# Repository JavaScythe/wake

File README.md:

The best alarm clock you'll ever meet.

An alexa without a microphone.

- 35 neopixels
- ESP32 with wifi
- Speaker
- Buzzer
- Projector

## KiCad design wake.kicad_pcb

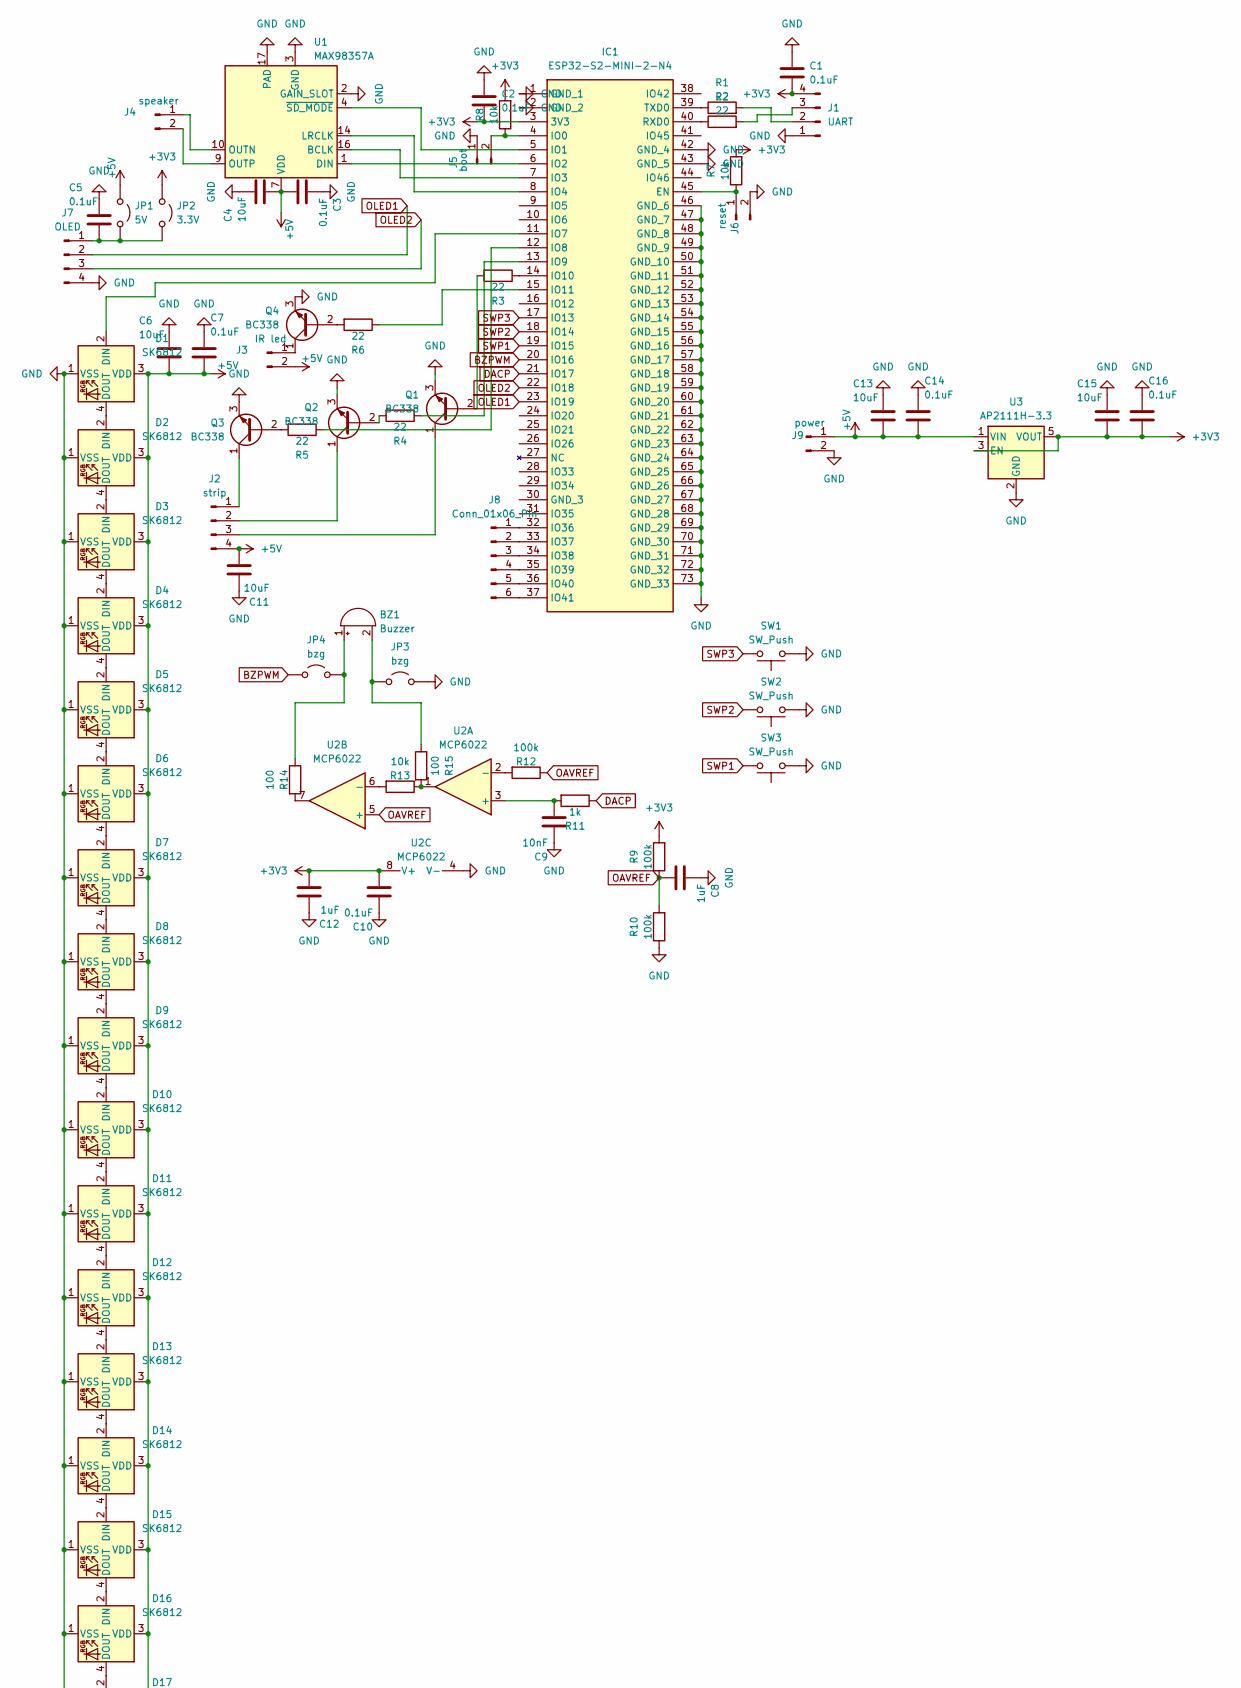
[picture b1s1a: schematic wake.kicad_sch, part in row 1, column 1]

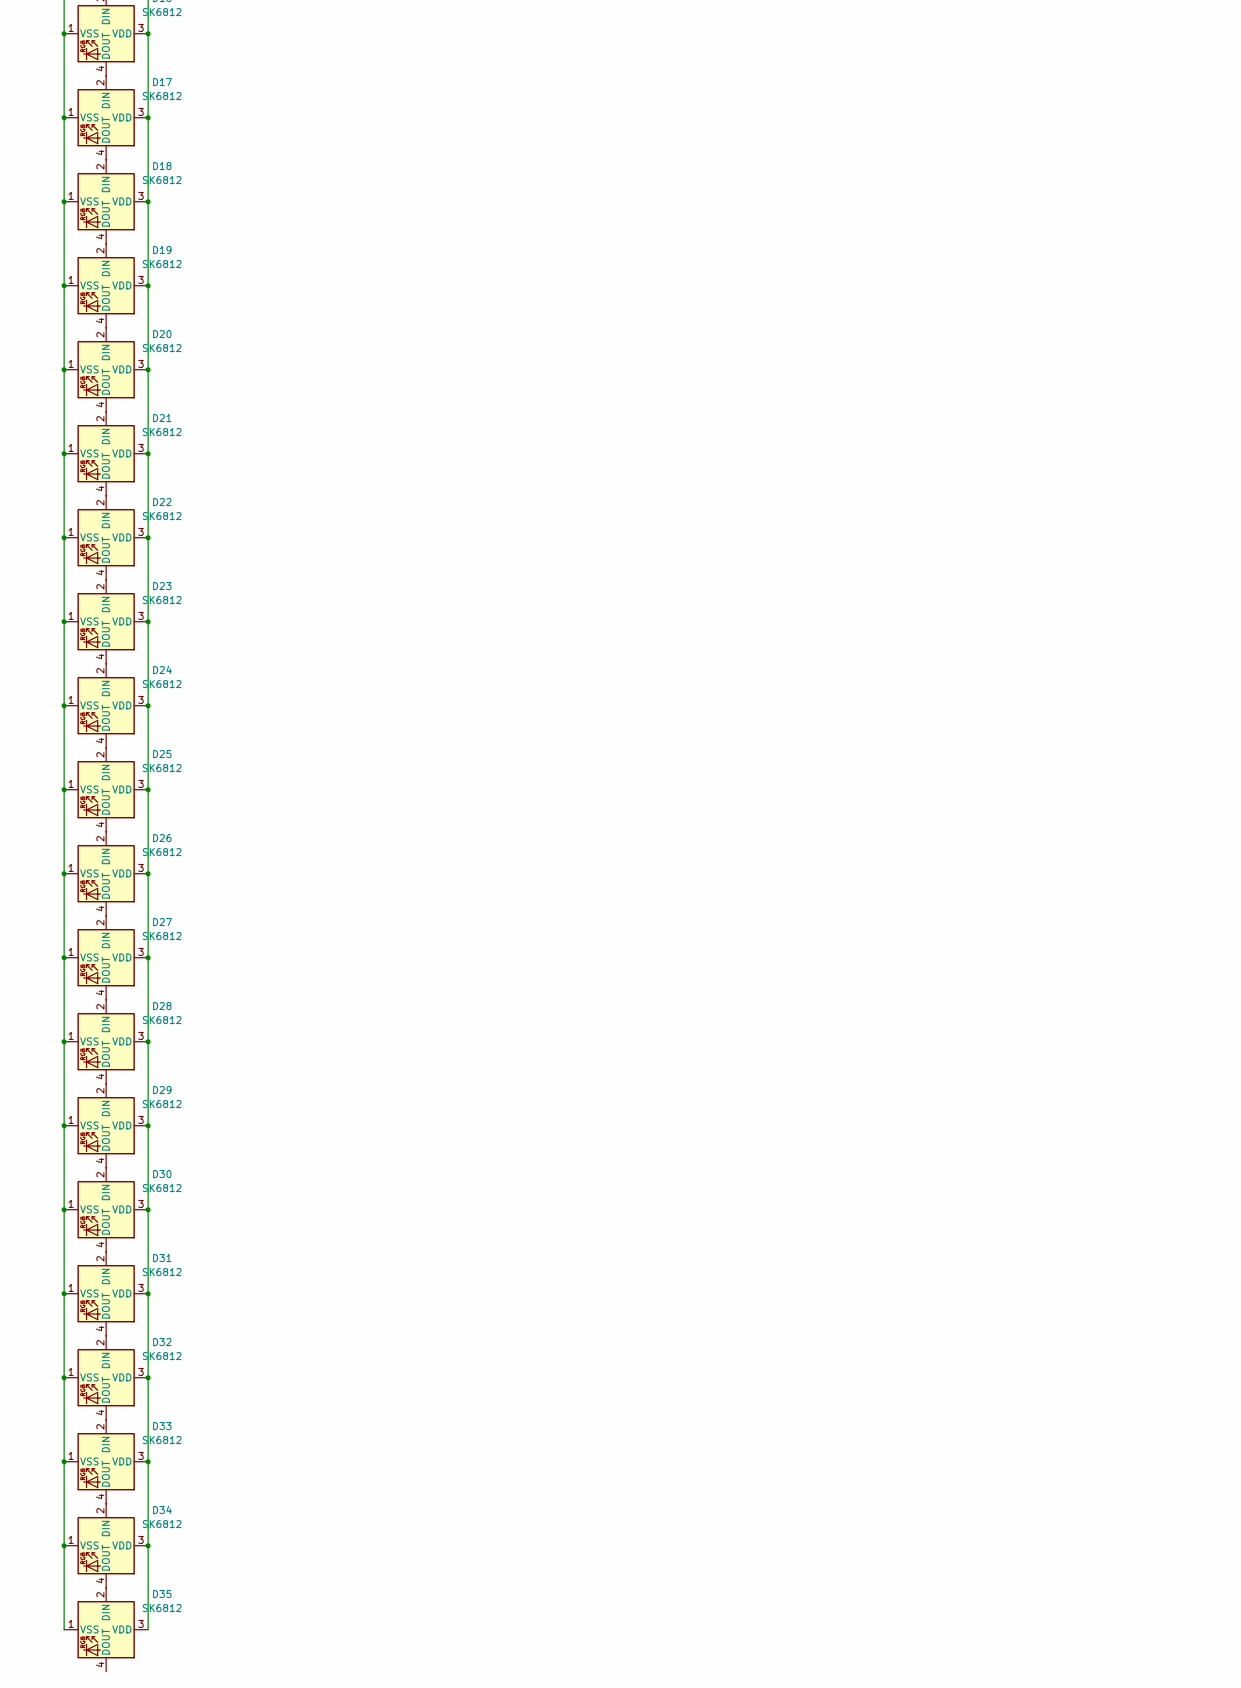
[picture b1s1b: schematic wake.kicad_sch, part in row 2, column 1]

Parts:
BZ1: Buzzer; Buzzer_12x9.5RM7.6
C1, C2, C3, C5, C7, C10, C14, C16: 0.1uF; C_0402_1005Metric
C4, C6, C11, C13, C15: 10uF; C_0402_1005Metric
C8, C12: 1uF; C_0402_1005Metric
C9: 10nF; C_0402_1005Metric
D1, D2, D3, D4, D5, D6, D7, D8, D9, D10, D11, D12, D13, D14, D15, D16, D17, D18, D19, D20, D21, D22, D23, D24, D25, D26, D27, D28, D29, D30, D31, D32, D33, D34, D35: SK6812; LED_SK6812_PLCC4_5.0x5.0mm_P3.2mm
IC1: ESP32-S2-MINI-2-N4; ESP32S2MINI2N4; Mouser Part Number 356-ESP32MINI-2-N4
J1: UART; PinHeader_1x04_P2.54mm_Vertical
J2: strip; PinHeader_1x04_P2.54mm_Vertical
J3: IR led; PinHeader_1x02_P2.54mm_Vertical
J4: speaker; PinHeader_1x02_P2.54mm_Vertical
J5: boot; PinHeader_1x02_P2.54mm_Vertical
J6: reset; PinHeader_1x02_P2.54mm_Vertical
J7: OLED; PinHeader_1x04_P2.54mm_Vertical
J8: Conn_01x06_Pin; PinHeader_1x06_P2.54mm_Vertical
J9: power; PinHeader_1x02_P2.54mm_Vertical
JP1: 5V; SolderJumper-2_P1.3mm_Open_TrianglePad1.0x1.5mm
JP2: 3.3V; SolderJumper-2_P1.3mm_Open_TrianglePad1.0x1.5mm
JP3, JP4: bzg; SolderJumper-2_P1.3mm_Open_TrianglePad1.0x1.5mm
Q1, Q2, Q3, Q4: BC338; TO-92_Inline
R1, R2, R3, R4, R5, R6: 22; R_0402_1005Metric
R7, R8, R13: 10k; R_0402_1005Metric
R9, R10, R12: 100k; R_0402_1005Metric
R11: 1k; R_0402_1005Metric
R14, R15: 100; R_0402_1005Metric
SW1, SW2, SW3: SW_Push; SW-SMD_4P-L12.0-W12.0-P5.00-LS15.5
U1: MAX98357A; TQFN-16-1EP_3x3mm_P0.5mm_EP1.23x1.23mm
U2: MCP6022; SOP-8_3.9x4.9mm_P1.27mm
U3: AP2111H-3.3; SOT-223

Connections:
+3V3: C1.2, C2.2, C10.2, C12.2, C15.2, C16.2, IC1.3 (3V3), J1.4, JP2.1 (A), R7.2, R8.2, R9.2, U2.8 (V+), U3.3 (EN), U3.5 (VOUT)
+5V: C3.2, C4.2, C6.2, C7.2, C11.2, C13.2, C14.2, D1.3 (VDD), D2.3 (VDD), D3.3 (VDD), D4.3 (VDD), D5.3 (VDD), D6.3 (VDD), D7.3 (VDD), D8.3 (VDD), D9.3 (VDD), D10.3 (VDD), D11.3 (VDD), D12.3 (VDD), D13.3 (VDD), D14.3 (VDD), D15.3 (VDD), D16.3 (VDD), D17.3 (VDD), D18.3 (VDD), D19.3 (VDD), D20.3 (VDD), D21.3 (VDD), D22.3 (VDD), D23.3 (VDD), D24.3 (VDD), D25.3 (VDD), D26.3 (VDD), D27.3 (VDD), D28.3 (VDD), D29.3 (VDD), D30.3 (VDD), D31.3 (VDD), D32.3 (VDD), D33.3 (VDD), D34.3 (VDD), D35.3 (VDD), J2.4, J3.2, J9.1, JP1.1 (A), U1.7 (VDD), U1.8 (VDD), U3.1 (VIN)
BZPWM: IC1.20 (IO16), JP4.1 (A)
DACP: IC1.21 (IO17), R11.1
GND: C1.1, C2.1, C3.1, C4.1, C5.1, C6.1, C7.1, C8.1, C9.1, C10.1, C11.1, C12.1, C13.1, C14.1, C15.1, C16.1, D1.1 (VSS), D2.1 (VSS), D3.1 (VSS), D4.1 (VSS), D5.1 (VSS), D6.1 (VSS), D7.1 (VSS), D8.1 (VSS), D9.1 (VSS), D10.1 (VSS), D11.1 (VSS), D12.1 (VSS), D13.1 (VSS), D14.1 (VSS), D15.1 (VSS), D16.1 (VSS), D17.1 (VSS), D18.1 (VSS), D19.1 (VSS), D20.1 (VSS), D21.1 (VSS), D22.1 (VSS), D23.1 (VSS), D24.1 (VSS), D25.1 (VSS), D26.1 (VSS), D27.1 (VSS), D28.1 (VSS), D29.1 (VSS), D30.1 (VSS), D31.1 (VSS), D32.1 (VSS), D33.1 (VSS), D34.1 (VSS), D35.1 (VSS), IC1.1 (GND_1), IC1.2 (GND_2), IC1.42 (GND_4), IC1.43 (GND_5), IC1.46 (GND_6), IC1.47 (GND_7), IC1.48 (GND_8), IC1.49 (GND_9), IC1.50 (GND_10), IC1.51 (GND_11), IC1.52 (GND_12), IC1.53 (GND_13), IC1.54 (GND_14), IC1.55 (GND_15), IC1.56 (GND_16), IC1.57 (GND_17), IC1.58 (GND_18), IC1.59 (GND_19), IC1.60 (GND_20), IC1.61 (GND_21), IC1.62 (GND_22), IC1.63 (GND_23), IC1.64 (GND_24), IC1.65 (GND_25), IC1.66 (GND_26), IC1.67 (GND_27), IC1.68 (GND_28), IC1.69 (GND_29), IC1.70 (GND_30), IC1.71 (GND_31), IC1.72 (GND_32), IC1.73 (GND_33), J1.1, J5.1, J6.2, J7.4, J9.2, JP3.2 (B), Q1.3 (E), Q2.3 (E), Q3.3 (E), Q4.3 (E), R10.1, SW1.1, SW2.1, SW3.1, U1.2 (GAIN_SLOT), U1.3 (GND), U1.11 (GND), U1.15 (GND), U1.17 (PAD), U2.4 (V-), U3.2 (GND)
unnamed: BZ1.1 (+), JP4.2 (B), R14.1
unnamed: BZ1.2 (-), JP3.1 (A), R15.1
unnamed: D1.2 (DIN), IC1.11 (IO7)
unnamed: D1.4 (DOUT), D2.2 (DIN)
unnamed: D2.4 (DOUT), D3.2 (DIN)
unnamed: D3.4 (DOUT), D4.2 (DIN)
unnamed: D4.4 (DOUT), D5.2 (DIN)
unnamed: D5.4 (DOUT), D6.2 (DIN)
unnamed: D6.4 (DOUT), D7.2 (DIN)
unnamed: D7.4 (DOUT), D8.2 (DIN)
unnamed: D8.4 (DOUT), D9.2 (DIN)
unnamed: D9.4 (DOUT), D10.2 (DIN)
unnamed: D10.4 (DOUT), D11.2 (DIN)
unnamed: D11.4 (DOUT), D12.2 (DIN)
unnamed: D12.4 (DOUT), D13.2 (DIN)
unnamed: D13.4 (DOUT), D14.2 (DIN)
unnamed: D14.4 (DOUT), D15.2 (DIN)
unnamed: D15.4 (DOUT), D16.2 (DIN)
unnamed: D16.4 (DOUT), D17.2 (DIN)
unnamed: D17.4 (DOUT), D18.2 (DIN)
unnamed: D18.4 (DOUT), D19.2 (DIN)
unnamed: D19.4 (DOUT), D20.2 (DIN)
unnamed: D20.4 (DOUT), D21.2 (DIN)
unnamed: D21.4 (DOUT), D22.2 (DIN)
unnamed: D22.4 (DOUT), D23.2 (DIN)
unnamed: D23.4 (DOUT), D24.2 (DIN)
unnamed: D24.4 (DOUT), D25.2 (DIN)
unnamed: D25.4 (DOUT), D26.2 (DIN)
unnamed: D26.4 (DOUT), D27.2 (DIN)
unnamed: D27.4 (DOUT), D28.2 (DIN)
unnamed: D28.4 (DOUT), D29.2 (DIN)
unnamed: D29.4 (DOUT), D30.2 (DIN)
unnamed: D30.4 (DOUT), D31.2 (DIN)
unnamed: D31.4 (DOUT), D32.2 (DIN)
unnamed: D32.4 (DOUT), D33.2 (DIN)
unnamed: D33.4 (DOUT), D34.2 (DIN)
unnamed: D34.4 (DOUT), D35.2 (DIN)
unnamed: IC1.45 (EN), J6.1, R7.1
unnamed: IC1.4 (IO0), J5.2, R8.1
unnamed: IC1.5 (IO1), U1.4 (~SD_MODE)
unnamed: IC1.6 (IO2), U1.1 (DIN)
unnamed: IC1.7 (IO3), U1.16 (BCLK)
unnamed: IC1.8 (IO4), U1.14 (LRCLK)
unnamed: IC1.12 (IO8), R5.1
unnamed: IC1.13 (IO9), R4.1
unnamed: IC1.14 (IO10), R3.1
unnamed: IC1.15 (IO11), R6.1
unnamed: IC1.32 (IO36), J8.1
unnamed: IC1.33 (IO37), J8.2
unnamed: IC1.34 (IO38), J8.3
unnamed: IC1.35 (IO39), J8.4
unnamed: IC1.36 (IO40), J8.5
unnamed: IC1.37 (IO41), J8.6
unnamed: IC1.40 (RXD0), R2.1
unnamed: IC1.39 (TXD0), R1.1
unnamed: J1.2, R1.2
unnamed: J1.3, R2.2
unnamed: J2.1, Q3.1 (C)
unnamed: J2.2, Q2.1 (C)
unnamed: J2.3, Q1.1 (C)
unnamed: J3.1, Q4.1 (C)
unnamed: J4.1, U1.10 (OUTN)
unnamed: J4.2, U1.9 (OUTP)
unnamed: C5.2, J7.1, JP1.2 (B), JP2.2 (B)
unnamed: Q1.2 (B), R3.2
unnamed: Q2.2 (B), R4.2
unnamed: Q3.2 (B), R5.2
unnamed: Q4.2 (B), R6.2
unnamed: R13.1, R15.2, U2.1
unnamed: R14.2, U2.7
unnamed: C9.2, R11.2, U2.3 (+)
unnamed: R12.2, U2.2 (-)
unnamed: R13.2, U2.6 (-)
OAVREF: C8.2, R9.1, R10.2, R12.1, U2.5 (+)
OLED1: IC1.23 (IO19), J7.2
OLED2: IC1.22 (IO18), J7.3
SWP1: IC1.19 (IO15), SW3.2
SWP2: IC1.18 (IO14), SW2.2
SWP3: IC1.17 (IO13), SW1.2

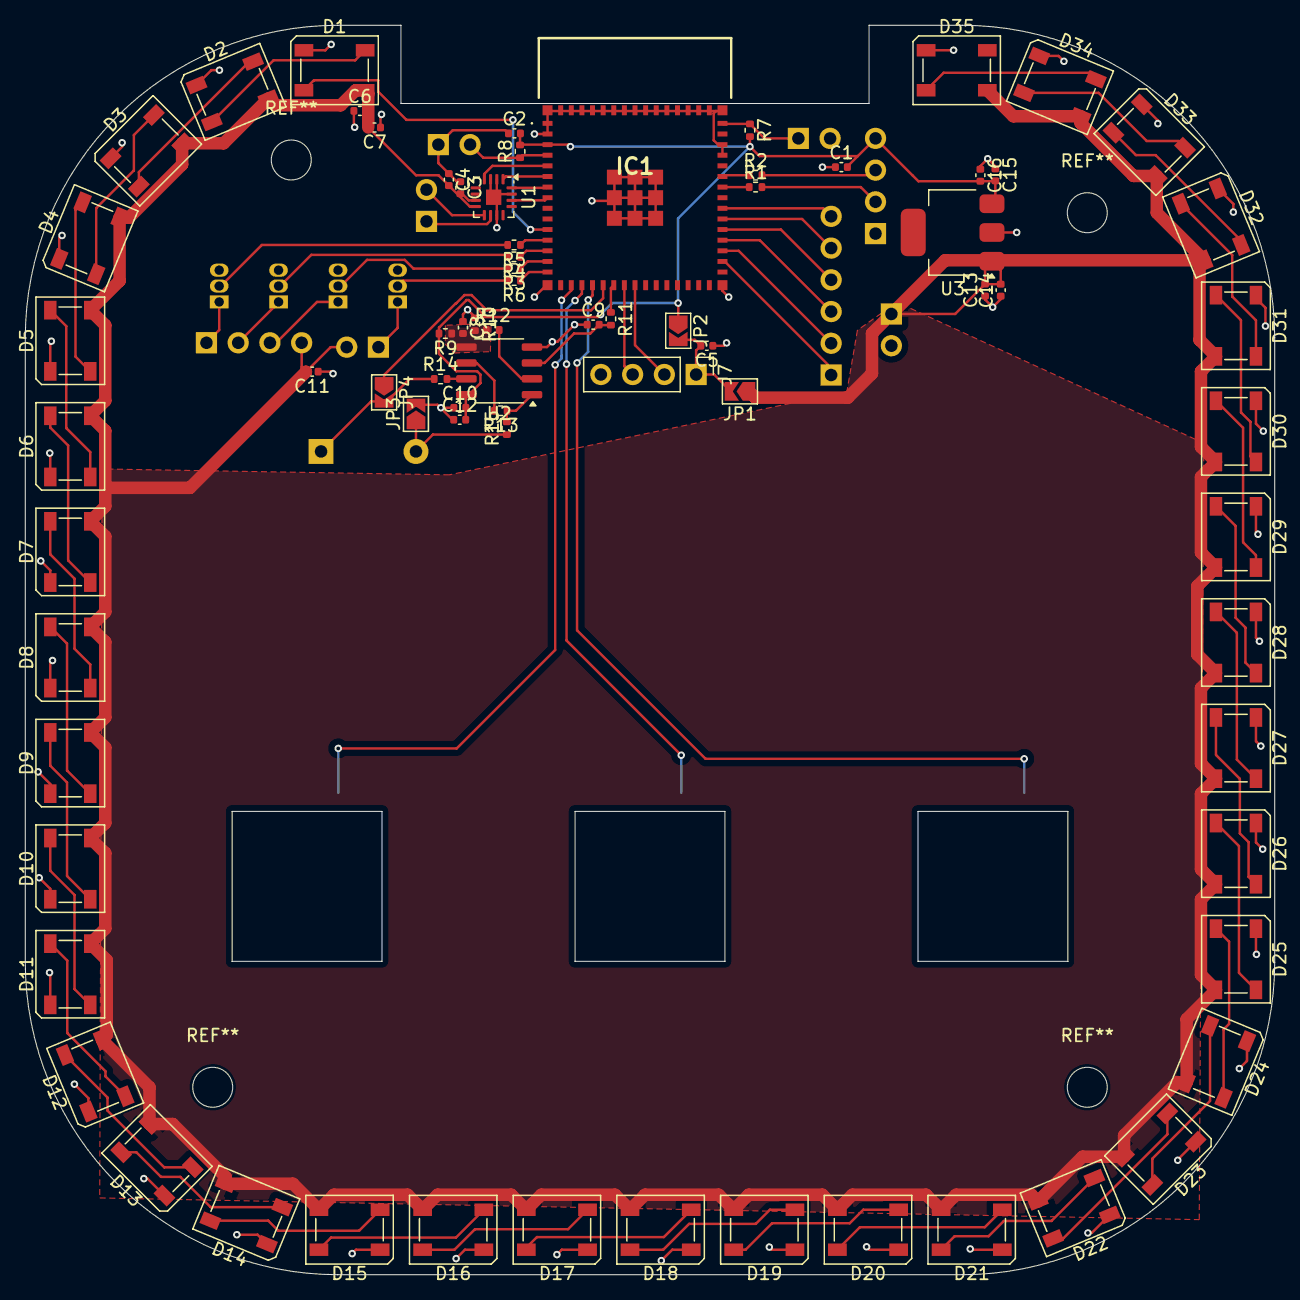
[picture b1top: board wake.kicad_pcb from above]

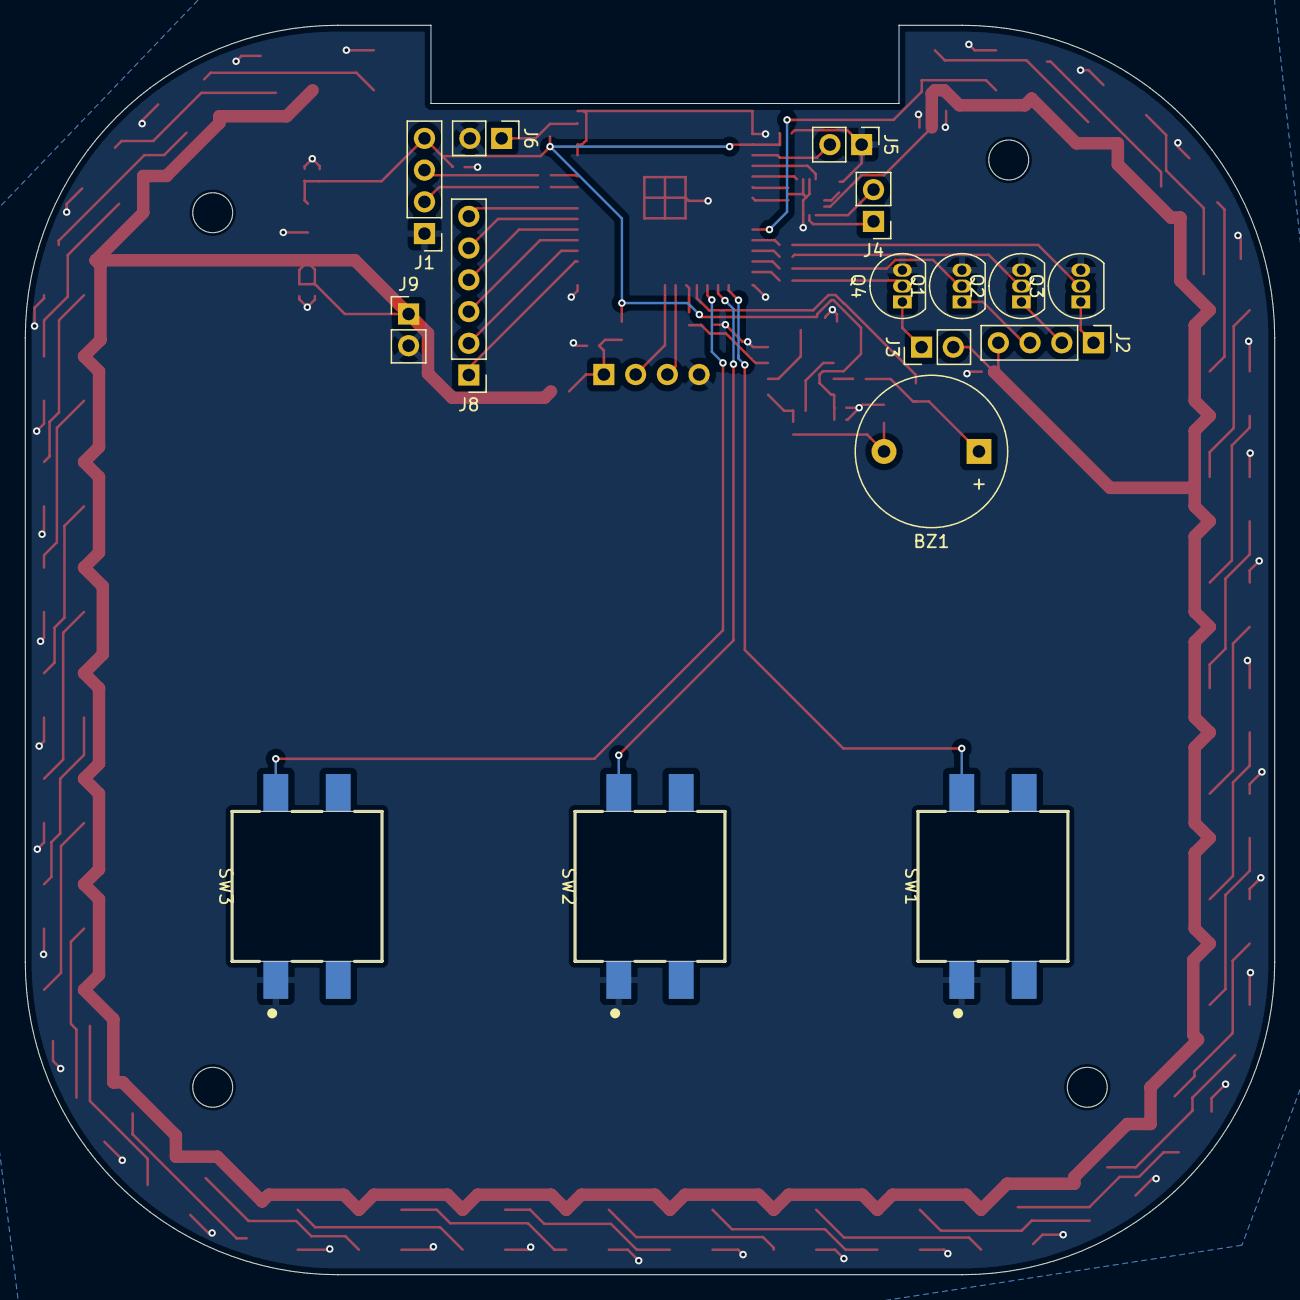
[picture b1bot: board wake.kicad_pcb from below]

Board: 2 copper layers, 100.0 x 100.0 mm, 91 parts (16 on the bottom side), 84 nets.
